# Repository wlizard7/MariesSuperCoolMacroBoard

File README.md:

# MariesSuperCoolMacroBoard
Hello, this is my submission for my hackpad. MariesSuperCoolMacroBoard! 

# PCB 

# CAD

The case was made in Fusion360. The case is three separate parts that are held together with 4 heatset inserts and screws! The PCB is held down with two more screws and heatset inserts.

# Firmware

The firmware was made using QMK. It uses the rotary encoder for volume, rotating it to change the volume up or down and pressing it to mute.

## Challenges
This was my first ever hardware project, although I did know some Fusion360 before starting. I came into this with no idea of what KiCad was or hardly any knowledge about hardware however I somehow 
figured things out AKA I watched a bunch of YouTube tutorials. Even with CAD experience, making the case was trickier than I thought it'd be, and I ended up having to remake both the PCB and case a few times. 

## Specifications

BOM : 

+ 1x Seeed XIAO RP2040
+ 9x 1N4148 Diodes
+ 1x 0.91 inch OLED display 
+ 1x EC11 Rotary encoder
+ 8x MX-Style switches
+ 8x Blank DSA keycaps
+ 4x SK6812 MINI-E LEDs
+ 6x M3x16mm screws
+ 6x M3x5mx4mm heatset inserts

## Notes
This was super fun! Three all nighters later, my project is done. I learned a lot through this process, and this has given me a whole lot of ideas of what to do next.

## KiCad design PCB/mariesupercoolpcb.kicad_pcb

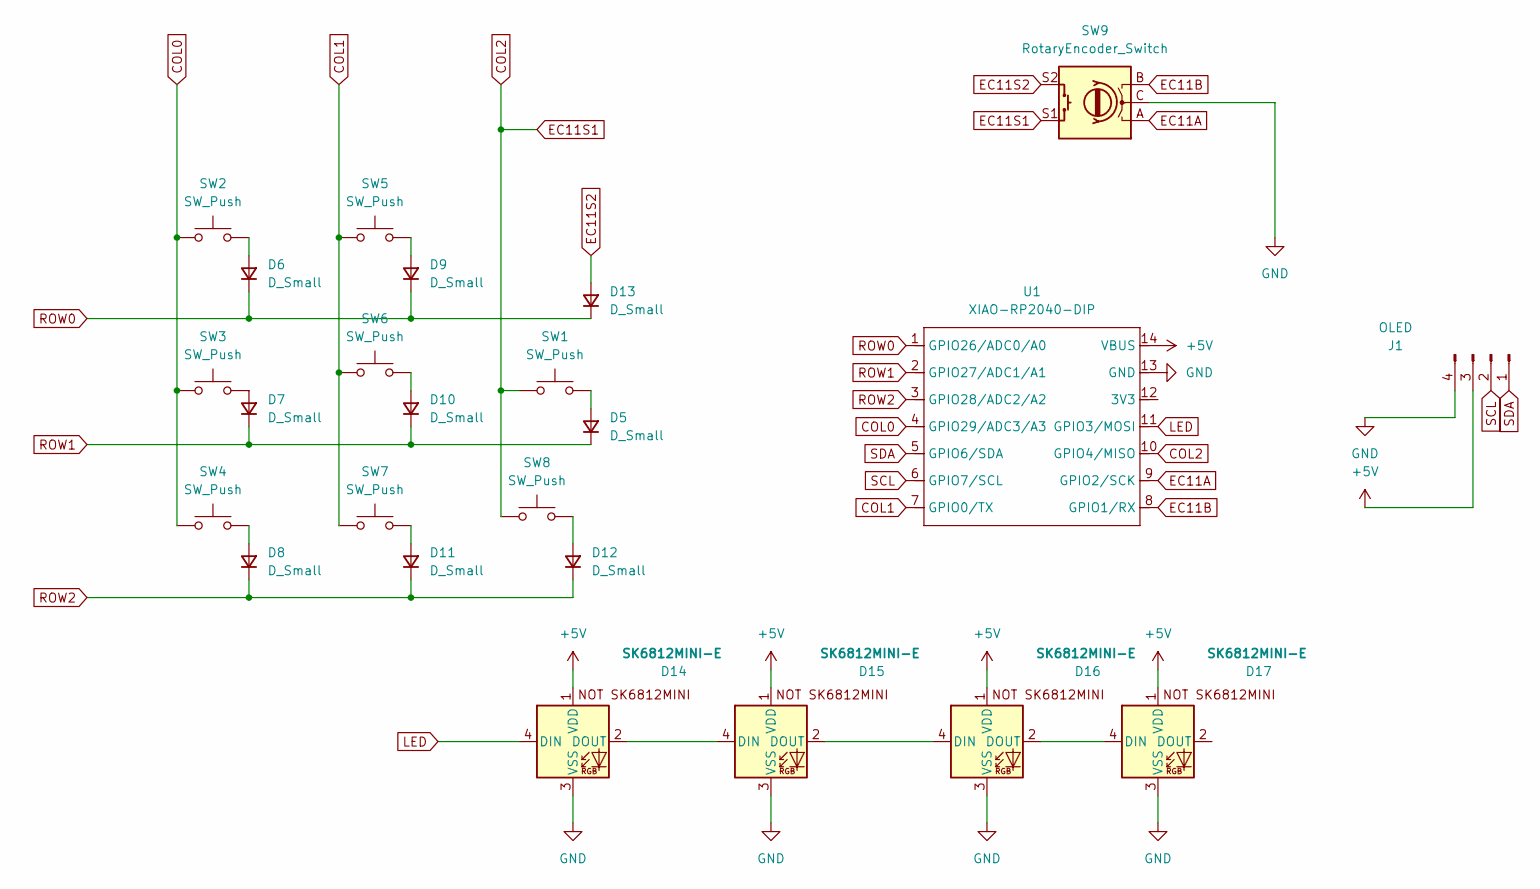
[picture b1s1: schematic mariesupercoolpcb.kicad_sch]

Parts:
D5, D6, D7, D8, D9, D10, D11, D12, D13: D_Small; D_DO-35_SOD27_P7.62mm_Horizontal
D14, D15, D16, D17: SK6812MINI-E; SK6812MINI-E_fixed
J1: OLED; SSD1306-0.91-OLED-4pin-128x32
SW1, SW2, SW3, SW4, SW5, SW6, SW7, SW8: SW_Push; SW_Cherry_MX_1.00u_PCB
SW9: RotaryEncoder_Switch; RotaryEncoder_Alps_EC11E-Switch_Vertical_H20mm
U1: XIAO-RP2040-DIP

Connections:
+5V: D14.1 (VDD), D15.1 (VDD), D16.1 (VDD), D17.1 (VDD), J1.3, U1.14 (VBUS)
COL0: SW2.1, SW3.1, SW4.1, U1.4 (GPIO29/ADC3/A3)
COL1: SW5.1, SW6.1, SW7.1, U1.7 (GPIO0/TX)
COL2: SW1.1, SW8.1, SW9.S1, U1.10 (GPIO4/MISO)
EC11A: SW9.A, U1.9 (GPIO2/SCK)
EC11B: SW9.B, U1.8 (GPIO1/RX)
EC11S2: D13.2 (A), SW9.S2
GND: D14.3 (VSS), D15.3 (VSS), D16.3 (VSS), D17.3 (VSS), J1.4, SW9.C, U1.13 (GND)
LED: D14.4 (DIN), U1.11 (GPIO3/MOSI)
unnamed: D5.2 (A), SW1.2
unnamed: D6.2 (A), SW2.2
unnamed: D7.2 (A), SW3.2
unnamed: D8.2 (A), SW4.2
unnamed: D9.2 (A), SW5.2
unnamed: D10.2 (A), SW6.2
unnamed: D11.2 (A), SW7.2
unnamed: D12.2 (A), SW8.2
unnamed: D14.2 (DOUT), D15.4 (DIN)
unnamed: D15.2 (DOUT), D16.4 (DIN)
unnamed: D16.2 (DOUT), D17.4 (DIN)
ROW0: D6.1 (K), D9.1 (K), D13.1 (K), U1.1 (GPIO26/ADC0/A0)
ROW1: D5.1 (K), D7.1 (K), D10.1 (K), U1.2 (GPIO27/ADC1/A1)
ROW2: D8.1 (K), D11.1 (K), D12.1 (K), U1.3 (GPIO28/ADC2/A2)
SCL: J1.2, U1.6 (GPIO7/SCL)
SDA: J1.1, U1.5 (GPIO6/SDA)

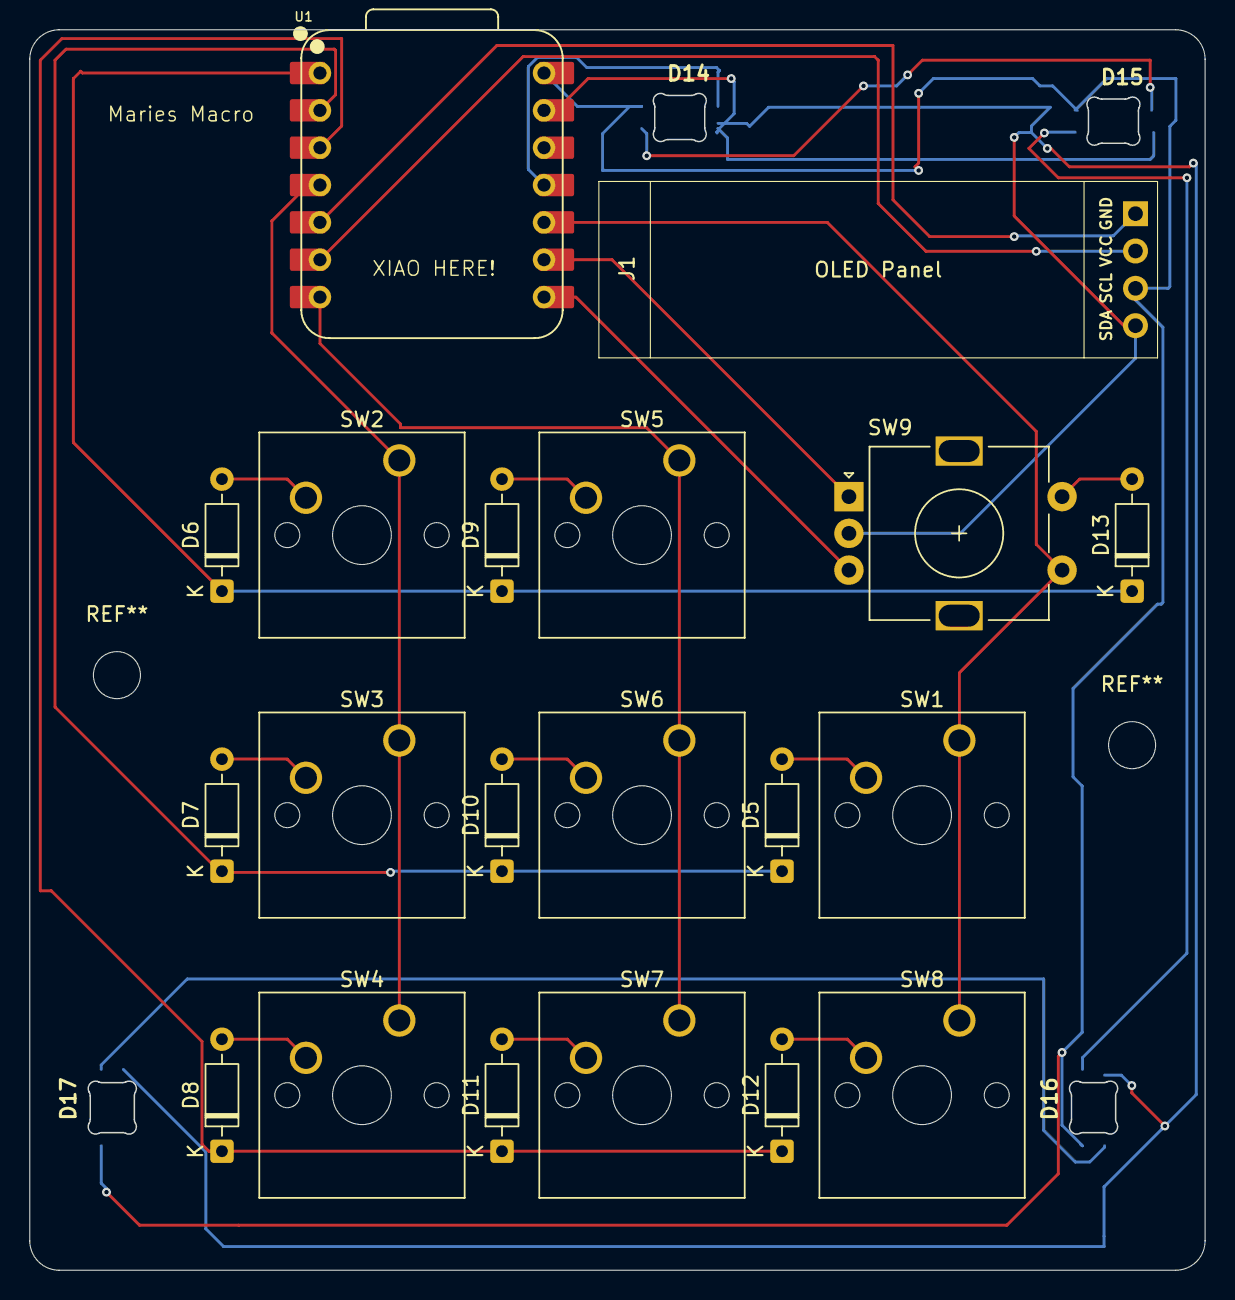
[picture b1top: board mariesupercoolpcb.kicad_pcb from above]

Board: 2 copper layers, 80.0 x 84.4 mm, 24 parts (0 on the bottom side), 25 nets.

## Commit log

2025-12-24 Added Files
2025-12-27 Updated PCB
2025-12-27 Firmware
